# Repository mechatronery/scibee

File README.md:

<table>
  <tr>
    <td width="120" align="center">
      
    </td>
    <td>
      <h1>Smart Community Integrated Beehive (SCIBee)</h1>
    </td>
  </tr>
</table>

SCIBee is an integrated beekeeping monitoring and management system combining beehive sensors, automated control hardware, entrance monitoring, camera-based bee detection, data aggregation, and AI-assisted colony assessment. It integrates local observations with agricultural and community data to support colony monitoring, seasonal assessment, and identification of potential risks, including Varroa mite infestations.

The system combines embedded controllers, Raspberry Pi computers, Python services, locally hosted AI models, and [OpenAgri](https://horizon-openagri.eu/) services. It supports two deployment modes: **Cloud Mode** and **Edge Mode**.

## System Overview

SCIBee consists of several interconnected subsystems:

- **Base Control System** — Measures beehive weight, treatment-agent mass, environmental conditions, and electrical parameters. It also supports automated treatment control.

- **Entrance Monitoring System** — Measures bee traffic, controls the entrance mechanism, and captures images for AI-assisted bee and Varroa monitoring.

- **Base Controller** — Uses a Raspberry Pi Zero 2 W to communicate with the base control boards over I²C, collect measurements, and provide a web interface for monitoring and control.

- **Observation Aggregator** — Processes sensor measurements and camera data, calculates statistics, performs image-based Varroa detection, and creates structured observations.

- **Beehive Evaluator** — Uses Qwen3-4B with `llama.cpp` to analyze aggregated observations and generate colony assessments and risk summaries.

- **OpenAgri Integration** — Connects SCIBee to Farm Calendar and related agricultural services for observations, weather data, and risk assessments.

- **Community Information System** — Collects community observations about flowering plants, meadow management, Varroa, and pesticide spraying.

- **Synchroniser** — Used for manual transfer of online observations to the Edge system.

- **Presenter** — Displays the latest AI-generated beehive evaluation retrieved from Farm Calendar.

The deployment mode determines where processing and AI inference run and whether external data integrations are directly available to the Aggregator.

## Deployment Modes

SCIBee supports two deployment modes that share the core beehive monitoring hardware and software but differ in processing infrastructure, connectivity, and data integration.

### Edge Mode

Edge Mode runs the main processing services and AI inference locally, close to the beehive powered exclusively by solar power.

- A Raspberry Pi Zero 2 W acts as the local base controller.
- A Raspberry Pi 5 hosts the Data Aggregator, Beehive Evaluator, Qwen3-4B inference server, and supporting services.
- The Raspberry Pi devices communicate over a local network.
- Sensor measurements and camera data are processed locally.
- Weather, risk, and community data integrations that require internet access are not available to the Aggregator.
- Observations from an online server can be transferred to the local Observation Store using a manually transferred synchronization file.

**Architecture:**

```mermaid
flowchart TB
    B["Beehive Sensors and Base Control Boards"]
    C["Entrance Camera — ESP32-S3-EYE"]
    EC["Entrance Counter — ESP32-C3"]

    G["Base Controller — Raspberry Pi Zero 2 W"]

    subgraph EDGE["Edge System — Raspberry Pi 5"]
        A["Data Aggregator<br/>(Local Observations)"]
        S[("Observation Store<br/>(OA-FarmCalendar)")]
        Y["Synchronizer"]
        E["Beehive Evaluator"]
        L["Qwen3-4B Inference Server<br/>llama.cpp"]
        P["Presenter"]
    end

    subgraph ONLINE["Online Server"]
        W["Weather and Risk Data<br/>(OA-WeatherService & PestAndDiseaseManagement)"]
        M["Community Observations"]
        OA["Data Aggregator<br/>(External Data)"]
        OS[("Observation Store<br/>(OA-FarmCalendar)")]

        W -->|"Weather and risk data"| OA
        M -->|"Community observations"| OA
        OA -->|"Aggregate and store observations"| OS
    end

    BK["Beekeeper"]

    B -->|"Sensor measurements"| G
    C -->|"Captured images / bee detections"| G
    EC -->|"Bee counts and entrance data"| G

    G -->|"Sensor data and images"| A

    A -->|"Store local aggregated observations"| S
    S -->|"Aggregated observations"| E

    OS -->|"Export synchronization file"| BK
    BK -->|"Manual file transfer"| Y
    Y -->|"Import observations"| S

    E <-->|"Inference requests / responses"| L
    E -->|"Generated colony summary"| P
    P -->|"Display summary"| BK

    classDef local fill:#dcefe3,stroke:#328052,color:#163c26
    classDef internet fill:#ffdada,stroke:#d62728,color:#8b1010
    classDef user fill:#fff0d1,stroke:#bd8a28,color:#63430b
    classDef online fill:#e0eaf9,stroke:#4778b8,color:#17365e

    class A,S,Y,E,L,P local
    class W,M internet
    class BK user
    class OA,OS,G online
```

### Cloud Mode

In Cloud Mode beehive data is collected by a remotely hosted processing environment.

- A Raspberry Pi Zero 2 W acts as the local base controller.
- A SIM7600G-H cellular modem provides LTE connectivity.
- A single cloud virtual machine hosts the Data Aggregator, Observation Store, Beehive Evaluator, and Qwen3-4B inference server.
- The Aggregator can integrate beehive data, external weather forecasts, risk assessments, and community observations.
- Tailscale provides private network connectivity for remote administration and access to connected devices and services.

**Architecture:**

```mermaid
flowchart TB
    B["Beehive Sensors and Base Control Boards"]
    C["Entrance Camera — ESP32-S3-EYE"]
    EC["Entrance Counter — ESP32-C3"]
    G["Base Controller — Raspberry Pi Zero 2 W"]
    N["LTE / Internet Connectivity"]

    subgraph CLOUD["Cloud System — Single Virtual Machine"]
        W["Weather and Risk Data<br/>(OA-WeatherService & PestAndDiseaseManagement)"]
        M["Community Observations"]
        A["Data Aggregator"]
        S[("Observation Store<br/>(OA-FarmCalendar)")]
        E["Beehive Evaluator"]
        L["Qwen3-4B Inference Server<br/>llama.cpp"]
        P["Presenter"]

        W -->|"Weather and risk data"| A
        M -->|"Community observations"| A
        A -->|"Aggregate and store observations"| S
        S -->|"Aggregated observations"| E
        E <-->|"Inference requests / responses"| L
        S -->|"Generated colony summary"| P
    end

    BK["Beekeeper"]

    B -->|"Sensor measurements"| G
    C -->|"Captured images / bee detections"| G
    EC -->|"Bee counts and entrance data"| G

    G -->|"Data transfer"| N
    N -->|"Sensor data and images"| A

    P -->|"Display summary"| BK

    classDef local fill:#dcefe3,stroke:#328052,color:#163c26
    classDef internet fill:#ffdada,stroke:#d62728,color:#8b1010
    classDef user fill:#fff0d1,stroke:#bd8a28,color:#63430b
    classDef network fill:#e0eaf9,stroke:#4778b8,color:#17365e

    class A,S,E,L,P local
    class W,M internet
    class BK user
    class G,N network
```

### Cloud vs. Edge

| Aspect                      | Cloud Mode              | Edge Mode                                                   |
| --------------------------- | ----------------------- | ----------------------------------------------------------- |
| Base controller             | Raspberry Pi Zero 2 W   | Raspberry Pi Zero 2 W                                       |
| Processing infrastructure   | Remote virtual machine  | Local Raspberry Pi 5                                        |
| Controller connectivity     | LTE modem               | Local Wi-Fi network                                         |
| AI inference                | Cloud server            | Local Raspberry Pi 5                                        |
| Weather and risk evaluation | Supported               | Skipped when observations are missing                       |
| Synchronization             | Automatic data transfer | Manual synchronization file transfer from the online server |
| Internet requirement        | Required                | Not required (only for online data)                         |

**Key distinction:** Cloud Mode centralizes processing and supports online data integrations. Edge Mode runs processing and AI inference locally, reducing dependence on remote infrastructure for core monitoring and evaluation, but requires manual synchronization of online observations.

## Hardware and Embedded Systems

### Base Control System

The Base Control System monitors beehive weight, treatment-agent mass, environmental conditions, and electrical parameters. Dedicated control boards communicate with the Raspberry Pi Zero 2 W over I²C.

- [Base Control System — Architecture and Hardware](SCIBee_Base/scibee_base_control_system.md)
- [Base Control Board — Firmware and I²C Protocol](SCIBee_Base/scibee_base_control_board_firmware.md)
- [Base Controller — Python Backend and Web Interface](SCIBee_Base/scibee_base_controller.md)
- [Base Stand — Mechanical Design](SCIBee_Base/scibee_base_stand.md)

### Entrance Monitoring System

The Entrance Monitoring System combines bee-traffic measurement, entrance control, and camera-based image capture.

The ESP32-C3-based entrance counter collects measurements from the entrance corridor array and controls the entrance mechanism. A separate ESP32-S3-EYE camera module captures images for AI-assisted bee detection and subsequent analysis.

- [Entrance System — Architecture and Hardware](SCIBee_Entrance/scibee_entrance_system.md)
- [Entrance Counter Corridor — Mechanical and Electrical Design](SCIBee_Entrance/scibee_entrance_counter_corridor.md)
- [Entrance Counter Corridor — Firmware](SCIBee_Entrance/scibee_entrance_counter_corridor_firmware.md)
- [Entrance Counter — Firmware](SCIBee_Entrance/scibee_entrance_counter_firmware.md)
- [Entrance Camera — Firmware and AI Detection](SCIBee_Entrance/scibee_entrance_camera_firmware.md)
- [Entrance and Camera — Firmware Programming Guide](SCIBee_Entrance/scibee_entrance_firmware_programming.md)

## Software Services and Data Processing

### Data Aggregator

The Data Aggregator collects beehive sensor measurements and camera data, calculates statistics, performs image-based Varroa detection, and creates structured observations in Farm Calendar.

Its execution mode determines whether external weather forecasts, risk assessments, and community observations are included.

See [SCIBee Aggregator](SCIBee_Data_Aggregator/scibee_aggregator.md).

### Beehive Evaluator

The Beehive Evaluator retrieves aggregated observations and submits them to a locally hosted Qwen3-4B language model through `llama.cpp`. It generates a structured assessment of colony conditions, seasonal development, and potential risks, then stores the result in Farm Calendar or the configured observation store.

See [SCIBee Evaluator](SCIBee_Evaluator/scibee_evaluator.md).

### OpenAgri Integration

The OpenAgri helper modules provide reusable Python functionality for interacting with agricultural services through REST APIs.

See [SCIBee Helper Functions for OpenAgri Services](SCIBee_OA_Functions/oa_functions.md).

### Community Information System

The Community Information System collects and shares local environmental information relevant to beekeeping, including flowering observations, meadow management, Varroa reports, and pesticide spraying.

See [SCIBee Community](SCIBee_Community/scibee_community.md).

### Synchroniser

The Synchroniser enables manual transfer of online observations to the local Edge Observation Store using a JSON file.

See [SCIBee Synchroniser](SCIBee_Synchroniser/scibee_synchroniser.md).

### Presenter

The Presenter retrieves the latest AI-generated beehive evaluation from Farm Calendar and displays the assessment details and evaluation age for a selected beehive.

See [SCIBee Presenter](SCIBee_Presenter/scibee_presenter.md).

## Getting Started

1. **Choose a deployment mode.** Use Cloud Mode for remote processing and online data integrations, or Edge Mode for local processing and AI inference.
2. **Configure the hardware.** Follow the relevant setup guide for the Raspberry Pi devices, networking, and required services.
3. **Deploy the Base Controller.** Configure I²C communication with the base control boards and verify local monitoring and control.
4. **Configure the software services.** Deploy the Aggregator and Evaluator, configure their service endpoints and execution mode, and set up the required OpenAgri services.
5. **Verify the data flow.** Confirm that sensor measurements and camera data are collected, observations are aggregated, and AI-generated evaluations are stored and available to the presentation layer.

**Note:** The system is **not yet plug-and-play**. Configuration must be reviewed and adapted to the specific hardware arrangement and network setup. Configuration examples may contain placeholder credentials, IP addresses, hostnames, and service URLs. Replace these with values appropriate for your deployment.

## Documentation Index

| Document                                                                                           | Description                                                                        |
| -------------------------------------------------------------------------------------------------- | ---------------------------------------------------------------------------------- |
| [Cloud Raspberry Pi Gateway Setup](SCIBee_Setup_Cloud/scibee_setup_cloud_rpi.md)                   | Gateway configuration, LTE connectivity, Tailscale, and Base Controller deployment |
| [Cloud Server Setup](SCIBee_Setup_Cloud/scibee_setup_cloud_server.md)                              | Virtual machine, Docker, AI inference, and service deployment                      |
| [Edge Raspberry Pi Setup](SCIBee_Setup_Edge/scibee_setup_edge_rpi.md)                              | Local networking, Raspberry Pi 5, AI inference, and service deployment             |
| [Observation Aggregator](SCIBee_Data_Aggregator/scibee_aggregator.md)                              | Data collection, processing modes, and observation integration                     |
| [Beehive Evaluator](SCIBee_Evaluator/scibee_evaluator.md)                                          | AI-based evaluation of aggregated beehive observations                             |
| [Base Controller](SCIBee_Base/scibee_base_controller.md)                                           | Python backend, web interface, measurement logging, and control                    |
| [Base Control System](SCIBee_Base/scibee_base_control_system.md)                                   | Hardware architecture and measurement components                                   |
| [Base Control Board Firmware](SCIBee_Base/scibee_base_control_board_firmware.md)                   | Embedded firmware and I²C command protocol                                         |
| [Base Stand](SCIBee_Base/scibee_base_stand.md)                                                     | Mechanical design and structural components                                        |
| [Entrance System](SCIBee_Entrance/scibee_entrance_system.md)                                       | Entrance monitoring hardware and architecture                                      |
| [Entrance Counter Corridor](SCIBee_Entrance/scibee_entrance_counter_corridor.md)                   | Corridor structure, electronics, and sensor arrangement                            |
| [Entrance Counter Corridor Firmware](SCIBee_Entrance/scibee_entrance_counter_corridor_firmware.md) | Corridor sensor firmware and I²C protocol                                          |
| [Entrance Counter Firmware](SCIBee_Entrance/scibee_entrance_counter_firmware.md)                   | Bee counting, entrance control, and data logging                                   |
| [Entrance Camera Firmware](SCIBee_Entrance/scibee_entrance_camera_firmware.md)                     | Camera operation, AI detection, image capture, and storage                         |
| [Firmware Programming Guide](SCIBee_Entrance/scibee_entrance_firmware_programming.md)              | Development environment, firmware uploads, and board configuration                 |
| [OpenAgri Helper Functions](SCIBee_OA_Functions/oa_functions.md)                                   | Python utilities for OpenAgri REST APIs                                            |
| [Community Information System](SCIBee_Community/scibee_community.md)                               | Community applications, architecture, and data handling                            |
| [Synchroniser](SCIBee_Synchroniser/scibee_synchroniser.md)                                         | Manual transfer of online observations to the Edge system                          |
| [Presenter](SCIBee_Presenter/scibee_presenter.md)                                                  | Displays the latest AI-generated beehive evaluation                                |

## Notes

- **Network configuration:** Use IP addresses, subnets, hostnames, and service URLs appropriate to your deployment.
- **Time synchronization:** Services and embedded devices use UTC timestamps. Ensure that clocks are synchronized and time settings are configured consistently across devices and services.
- **Treatment decisions:** Sensor measurements and AI-generated assessments are decision-support tools. Follow applicable product instructions and veterinary guidance when making treatment decisions.

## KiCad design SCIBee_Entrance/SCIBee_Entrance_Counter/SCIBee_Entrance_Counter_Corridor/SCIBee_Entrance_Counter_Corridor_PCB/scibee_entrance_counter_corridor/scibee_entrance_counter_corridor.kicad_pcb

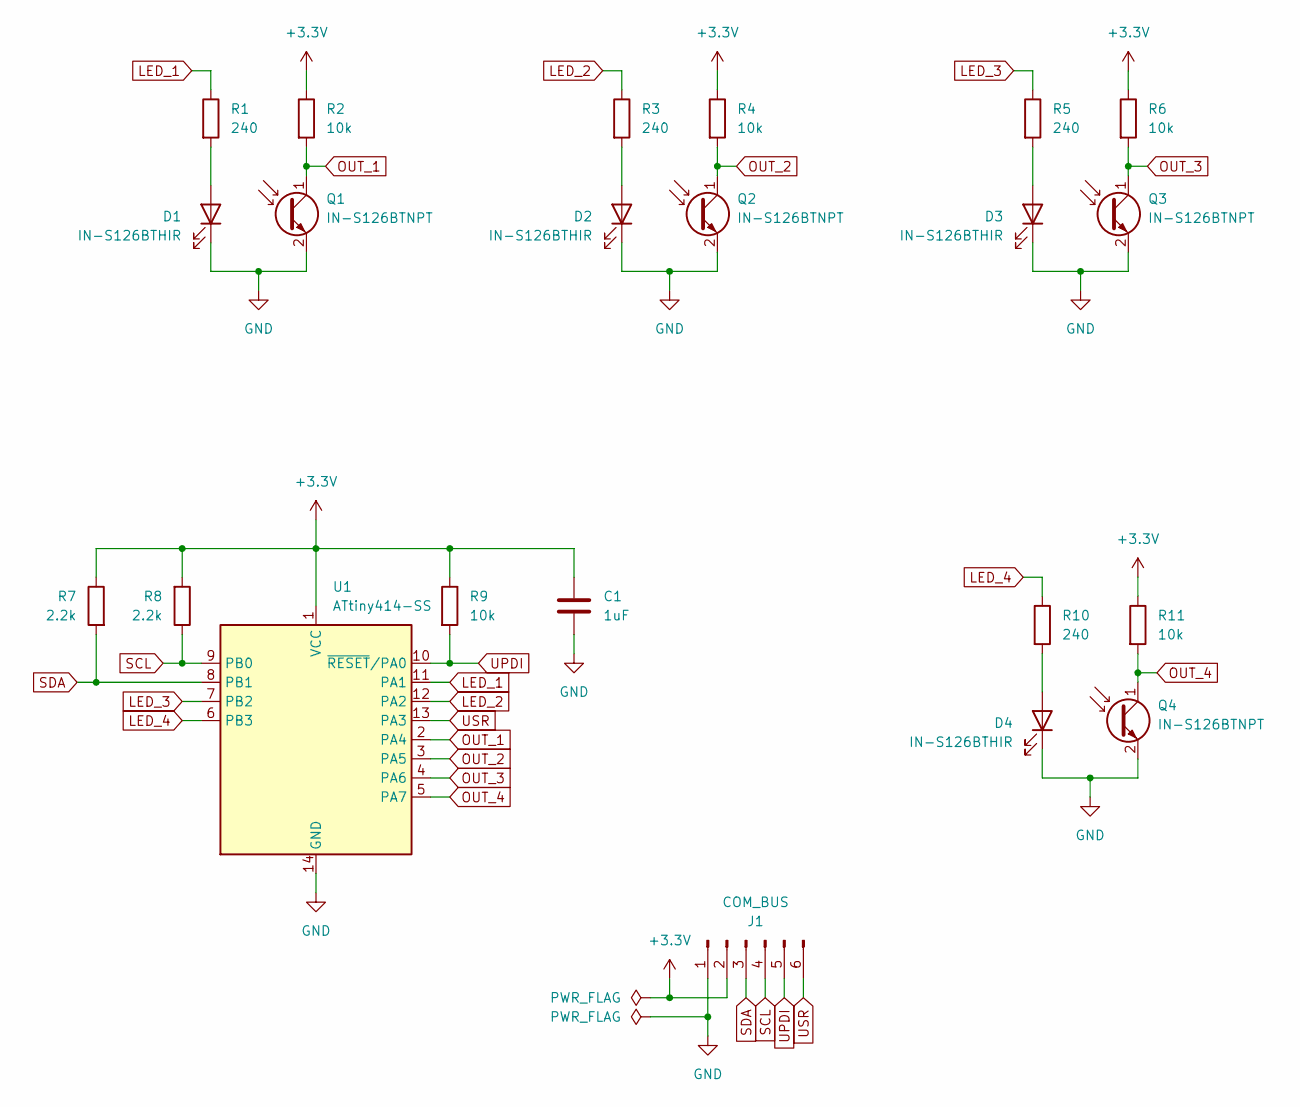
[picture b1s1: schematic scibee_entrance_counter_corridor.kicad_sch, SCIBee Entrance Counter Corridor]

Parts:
C1: 1uF; C_1206_3216Metric_Pad1.33x1.80mm_HandSolder
D1, D2, D3, D4: IN-S126BTHIR; LED_1206_3216Metric_Pad1.42x1.75mm_HandSolder
J1: COM_BUS; PinSocket_1x06_P2.54mm_Vertical
Q1, Q2, Q3, Q4: IN-S126BTNPT; LED_1206_3216Metric_Pad1.42x1.75mm_HandSolder
R1, R3, R5, R10: 240; R_1206_3216Metric_Pad1.30x1.75mm_HandSolder
R2, R4, R6, R9, R11: 10k; R_1206_3216Metric_Pad1.30x1.75mm_HandSolder
R7, R8: 2.2k; R_1206_3216Metric_Pad1.30x1.75mm_HandSolder
U1: ATtiny414-SS; SOIC-14_3.9x8.7mm_P1.27mm

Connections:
+3.3V: C1.2, J1.2, R2.1, R4.1, R6.1, R7.1, R8.2, R9.1, R11.1, U1.1 (VCC)
GND: C1.1, D1.1 (K), D2.1 (K), D3.1 (K), D4.1 (K), J1.1, Q1.2 (E), Q2.2 (E), Q3.2 (E), Q4.2 (E), U1.14 (GND)
LED_1: R1.1, U1.11 (PA1)
LED_2: R3.1, U1.12 (PA2)
LED_3: R5.1, U1.7 (PB2)
LED_4: R10.1, U1.6 (PB3)
unnamed: D1.2 (A), R1.2
unnamed: D2.2 (A), R3.2
unnamed: D3.2 (A), R5.2
unnamed: D4.2 (A), R10.2
OUT_1: Q1.1 (C), R2.2, U1.2 (PA4)
OUT_2: Q2.1 (C), R4.2, U1.3 (PA5)
OUT_3: Q3.1 (C), R6.2, U1.4 (PA6)
OUT_4: Q4.1 (C), R11.2, U1.5 (PA7)
SCL: J1.4, R8.1, U1.9 (PB0)
SDA: J1.3, R7.2, U1.8 (PB1)
UPDI: J1.5, R9.2, U1.10 (~RESET/PA0)
USR: J1.6, U1.13 (PA3)

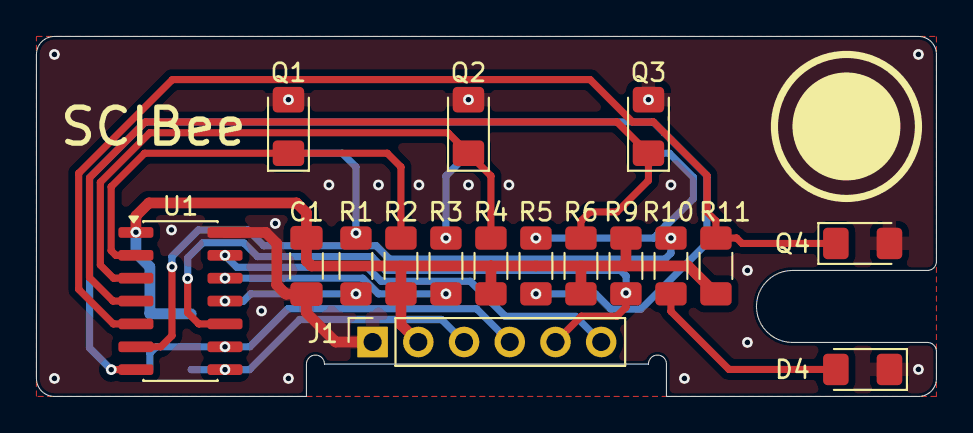
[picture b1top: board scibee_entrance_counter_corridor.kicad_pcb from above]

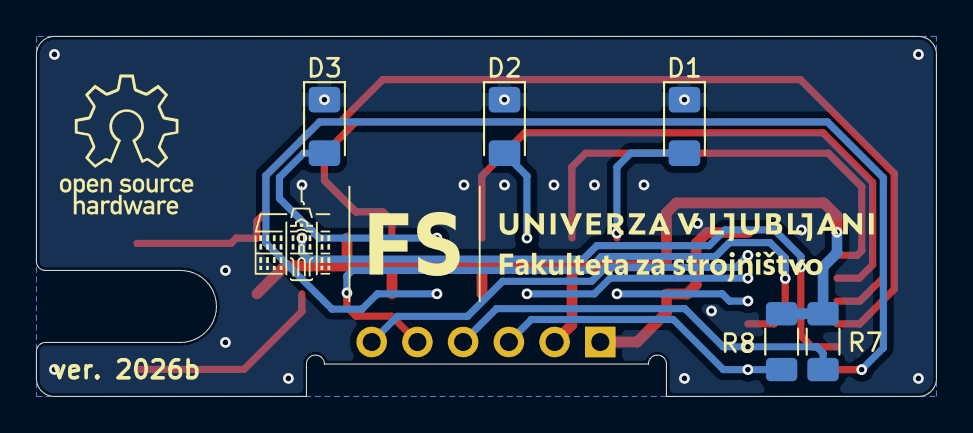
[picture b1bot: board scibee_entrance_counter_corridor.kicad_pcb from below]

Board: 2 copper layers, 50.0 x 20.0 mm, 22 parts (5 on the bottom side), 18 nets.

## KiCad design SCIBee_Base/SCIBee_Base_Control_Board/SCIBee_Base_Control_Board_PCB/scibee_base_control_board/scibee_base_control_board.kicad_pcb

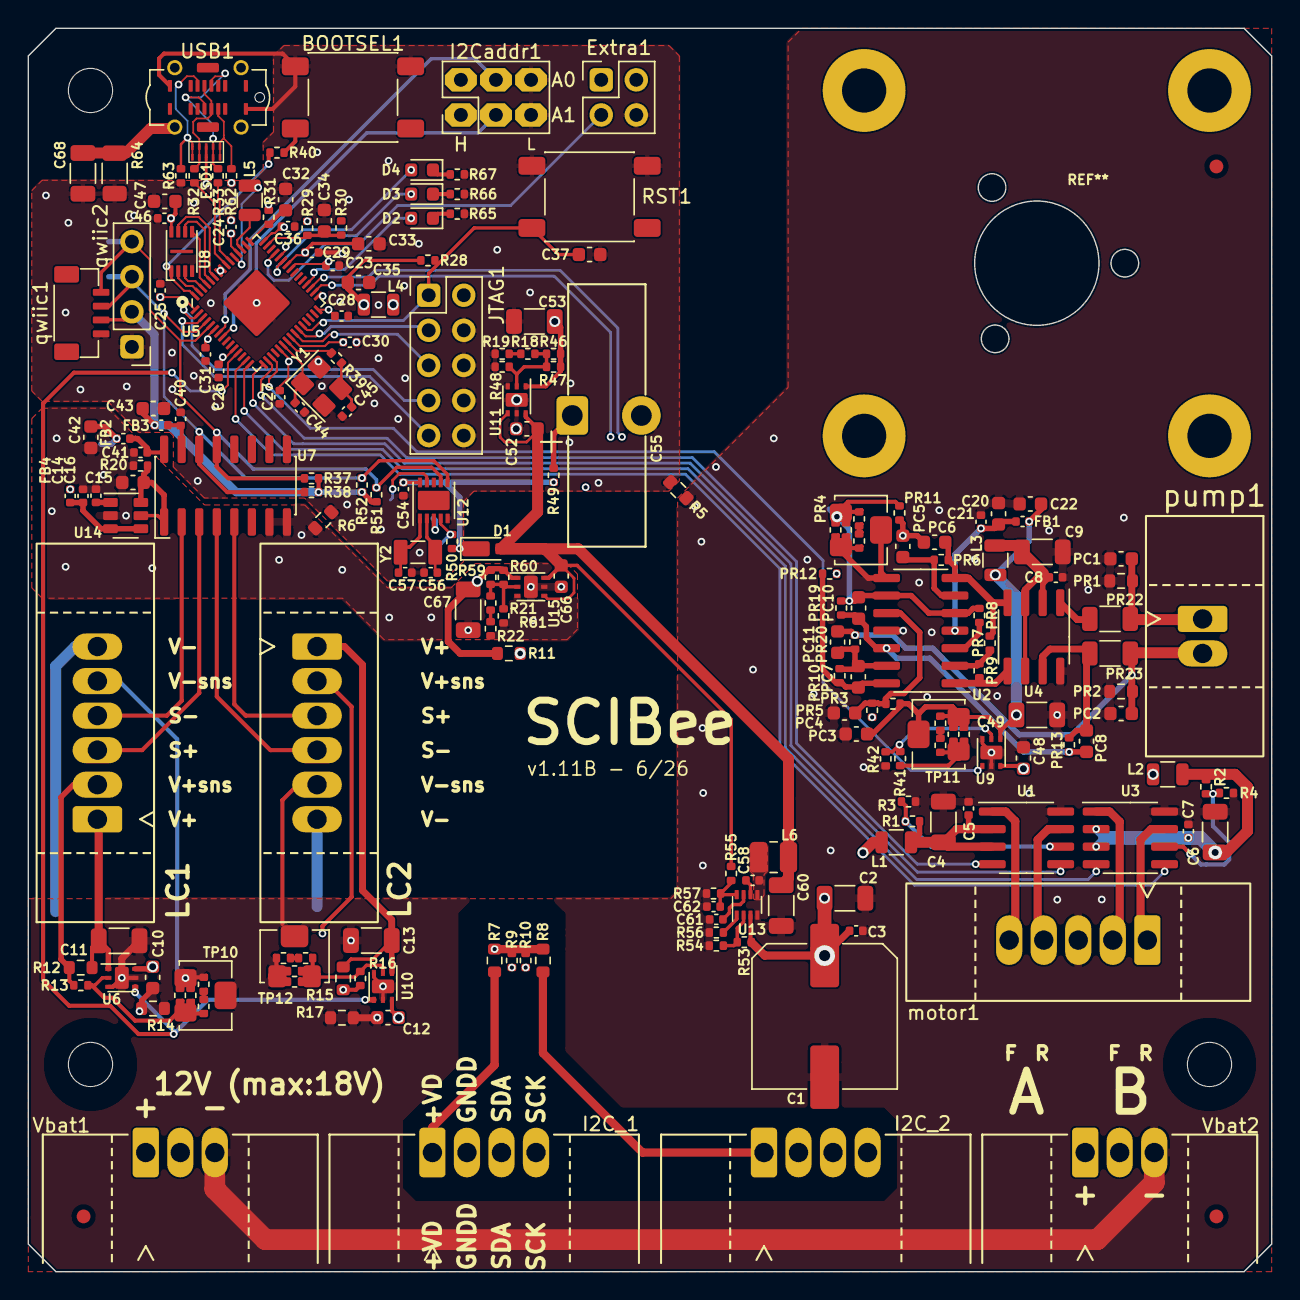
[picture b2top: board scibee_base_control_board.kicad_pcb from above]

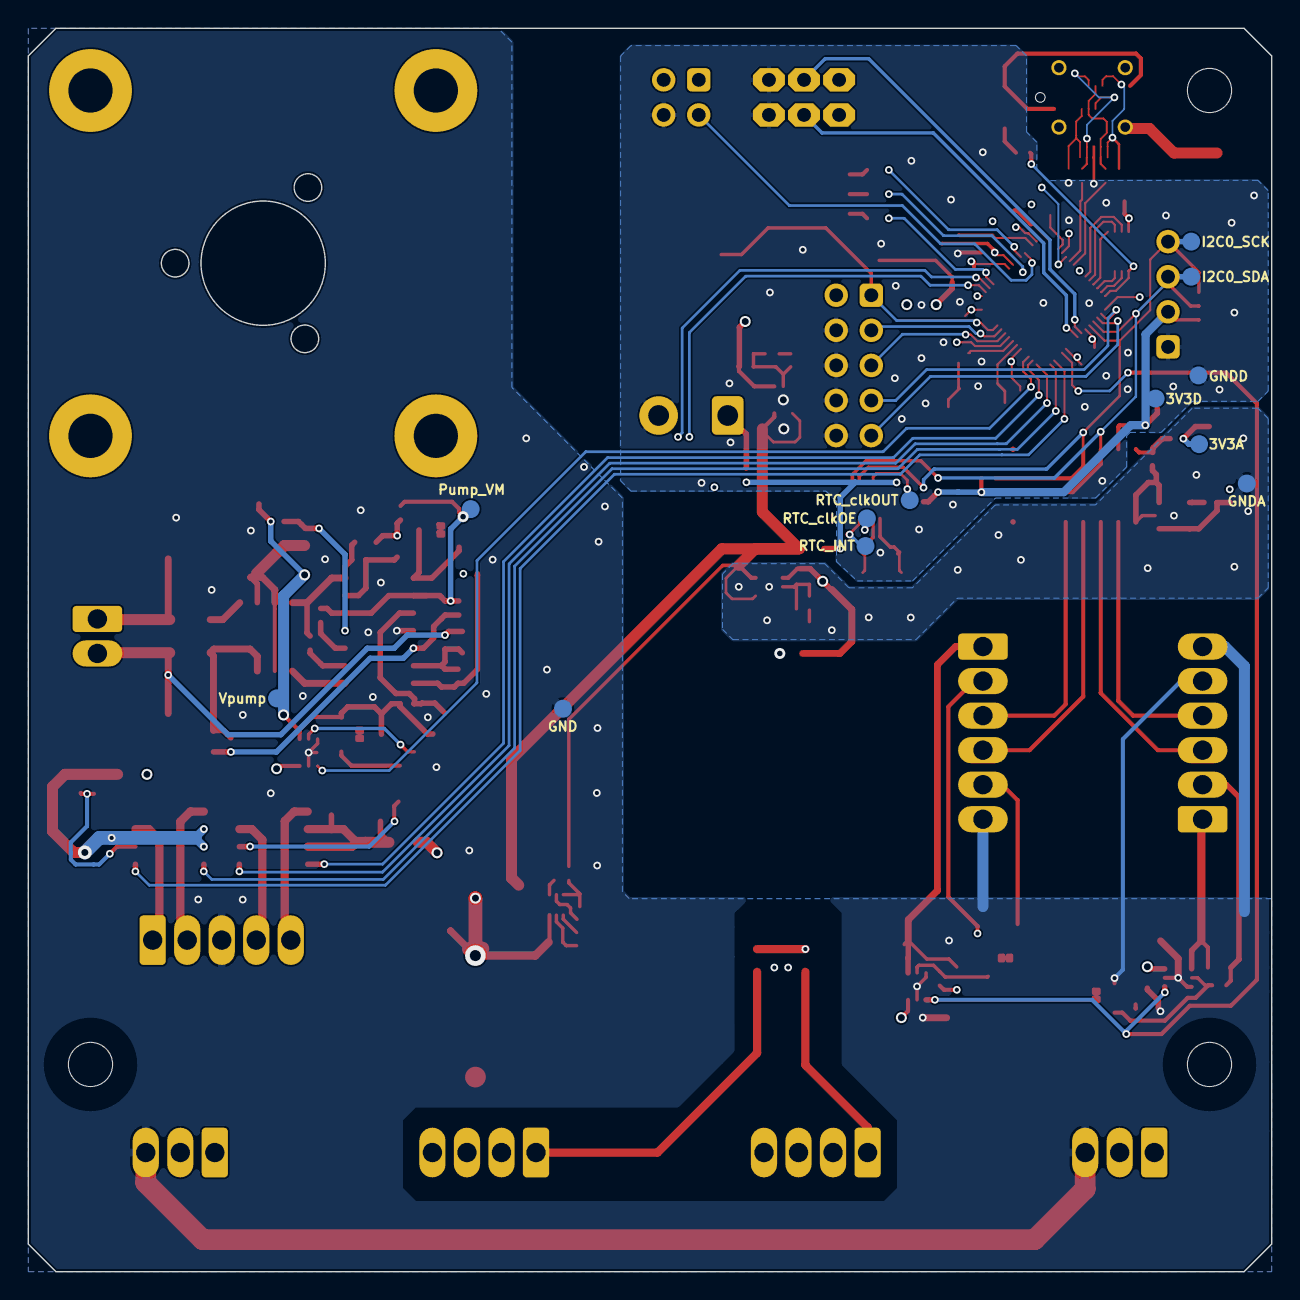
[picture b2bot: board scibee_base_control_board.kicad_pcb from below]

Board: 4 copper layers, 90.0 x 90.0 mm, 208 parts (12 on the bottom side), 118 nets.

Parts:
BOOTSEL1: SW_Momentary_NO; SW_PUSH_6mm_SMD
C1: Capacitor_pol; C_AlElec_SMD-10x10.2
C2, C4, C6, C9, C11, C13, C49, C53, C60, C67: 10uF; C_1206_(3216)
C3, C5, C7, C8, C14, C16, C21, C23, C24, C25, C26, C27, C28, C29, C30, C31, C36, C40, C41, C46, C54, C58, C61: 100nF; C_0402_(1005)
C10, C12, C15, C20, C22, C37, C42, C43, C48, C52, C66: 1uF; C_0603_(1608)
C32, C33, C34, C35, C47: 4u7F; C_0603_(1608)
C44, C45: 15pF; C_0402_(1005)
C55: 1F; C_Supercap_D18.7mm_P5.00mm_Vertical
C56, C57: -; C_0402_(1005)
C62: cap; C_0402_(1005)
C68: 2n2F; C_1206_(3216)
D1: RF05VAM1STR; D_DO-219AD_(microSMP)
D2: red; LED_0603_(1608)
D3: yellow; LED_0603_(1608)
D4: green; LED_0603_(1608)
ESD1: PUSB3FA2Z; DFN2510A-10
Extra1: 0.1" 2x2 header; Header_Pin_THT_Vertical_P2.54mm_2x02
FB1, FB2, FB3, FB4: FB600; L_0402_(1005)
FID1, FID2, FID3: Fiducial; Fiducial_1mm+2mm
I2C_1, I2C_2: TerminalBlock_2.5mm_Horizontal; TerminalBlock_1x04_P2.5mm_Horizontal_Screw
I2Caddr1: 0.1" 2x03 header; Header_Pin_THT_Vertical_P2.54mm_2x03
JTAG1: Conn_02x05; Header_Pin_THT_Vertical_P2.54mm_2x05
L1, L2, L3, L4, L5: 4u7H; L_0806_(2016)
L6: 22uH; L_1008_(2520)
LC1, LC2: TerminalBlock_2.5mm_Horizontal; TerminalBlock_1x06_P2.5mm_Vertical_Screw
M1, M3, M4: Mounting_hole; MountingHole_M3
PC1, PC2: 15pF; C_0603_(1608)
PC3, PC4: 1uF; C_0603_(1608)
PC5, PC6: 1nF; C_0603_(1608)
PC7, PC10: 10pF; C_0603_(1608)
PC8, PC11: 100pF; C_0603_(1608)
PR1, PR2: 1M; R_0603_(1608)
PR3, PR5, PR10, PR19: 470k; R_0402_(1005)
PR4: 10k; PVG5A
PR6: 68k; R_0402_(1005)
PR7, PR8, PR9: 10k; R_0402_(1005)
PR11: 390; R_0402_(1005)
PR12, PR13, PR20: 1k5; R_0402_(1005)
PR22, PR23: 10; R_1206_(3216)
R1, R2: 0; R_0402_(1005)
R3, R4, R30: -; R_0402_(1005)
R5, R6, R11: 0; R_0603_(1608)
R7, R8, R12, R14, R15, R17: -; R_0603_(1608)
R9, R10, R18, R21, R37, R38, R51, R52, R62, R63: 5k1; R_0402_(1005)
R13, R16, R41, R46, R47, R59, R60: 470k; R_0402_(1005)
R19, R22, R28, R42, R48, R61: 68k; R_0402_(1005)
R20, R50, R54, R56, R57: 10k; R_0402_(1005)
R29: 390R; R_0402_(1005)
R31, R32, R33: 27R; R_0402_(1005)
R39, R40: 1k5; R_0402_(1005)
R49, R65, R66, R67: 390; R_0402_(1005)
R53, R55: 39k; R_0402_(1005)
R64: 1M; R_1206_(3216)
RST1: SW_Momentary_NO; SW_PUSH_6mm_SMD
TP1: 3V3D; TestPoint
TP2: Pump_VM; TestPoint
TP3: 3V3A; TestPoint
TP4: GND; TestPoint
TP5: I2C0_SDA; TestPoint
TP6: I2C0_SCK; TestPoint
TP7: RTC_INT; TestPoint
TP8: RTC_clkOE; TestPoint
TP9: RTC_clkOUT; TestPoint
TP10, TP11, TP12: 500k; PVG5A
TP13: GNDA; TestPoint
TP14: GNDD; TestPoint
TP15: Vpump; TestPoint
U1, U3, U4: BD6231F-E2; SOIC-8_3.9x4.9mm_P1.27mm
U2: NCV274; SOIC-14_3.9x8.7mm_P1.27mm
U5: RP2350A; QFN-60-EP1_7x7mm_P0.4mm_EP3.4mm
U6, U9, U10, U11, U15: TPS7A2601; DFN-6-1EP_2x2mm_P0.65mm
U7: NAU7802SGI; SOIC-16_3.9x9.9mm_P1.27mm
U8: W25Q32RV; XSON-8-EP_2x3mm_P0.5mm_EP0.2x1.6mm
U12: PCF85063A; DFN-10_2.6x2.6_P0.5
U13: TPS62932; SOT-5X3-8
U14: MAX6070BAUT21+T; SOT-23-6
USB1: USB_C_USB2.0; USB_C_GCT_USB4220_Vertical
Vbat1, Vbat2: TerminalBlock_2.5mm_Horizontal; TerminalBlock_1x03_P2.5mm_Horizontal_Screw
Y1: 12MHz; Crystal_SMD_3225-4Pin_3.2x2.5mm
Y2: 32.768kHz; Crystal_SMD_TXC_9HT10
motor1: TerminalBlock_2.5mm_Horizontal; TerminalBlock_1x05_P2.5mm_Vertical_Screw
pump1: TerminalBlock_2.5mm_Vertical; TerminalBlock_1x02_P2.5mm_Vertical_Screw
qwiic1: SIO_SPARKFUN_qwiic; JST_SMD_Vertical_P1.00mm_BM04B
qwiic2: Conn_01x04; Header_Pin_THT_Vertical_P2.54mm_1x04

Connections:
+3.3VA: C42.1, C67.1, FB2.1, FB4.1, R11.2, R59.1, R60.1, TP3.1, U15.1 (Vout)
+3.3VD: C43.1, C53.1, Extra1.1, FB3.1, I2Caddr1.1, I2Caddr1.2, JTAG1.2, L4.2, R7.1, R8.1, R9.1, R10.1, R11.1, R37.1, R38.1, R46.1, R47.1, R51.1, R52.1, TP1.1, U11.1 (Vout), qwiic1.2 (3V3), qwiic2.2
+Vbat: C1.+, C2.1, C3.1, C10.1, C12.1, C48.1, L1.1, L2.1, R53.2, U6.6 (Vin), U9.6 (Vin), U10.6 (Vin), U13.3 (Vin), Vbat1.1, Vbat2.1
/+4V: C52.1, C60.1, C66.1, D1.A, L6.2, R55.1, U11.4 (EN), U11.6 (Vin), U15.4 (EN), U15.6 (Vin)
/H-bridge/VrefA: R1.2, R3.1, U1.6 (Vref)
/H-bridge/VrefB: R2.2, R4.1, U3.6 (Vref)
/I2C0_SCK: R37.2, R51.2, TP6.1, U5.5 (GPIO_3/SPI0_MOSI/UART0_RTS/I2C1_SCL/PWM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), U7.13 (SCK), U12.7 (SCL), qwiic1.4 (SCK), qwiic2.4
/I2C0_SDA: R38.2, R52.2, TP5.1, U5.4 (GPIO_2/SPI0_SCK/UART0_CTS/I2C1_SDA/PWM1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), U7.14 (SDA), U12.6 (SDA), qwiic1.3 (SDA), qwiic2.3
/I2C1_SCK: I2C_1.4, I2C_2.4, R10.2, U5.33 (GPIO_21/SPI0_CSn/UART1_RX/I2C0_SCL/PWM2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)
/I2C1_SDA: I2C_1.3, I2C_2.3, R9.2, U5.32 (GPIO_20/SPI0_MISO/UART1_TX/I2C0_SDA/PWM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)
/LC_enable: U5.12 (GPIO_8/SPI1_MISO/UART1_TX/I2C0_SDA/PWM4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), U6.4 (EN), U10.4 (EN)
/Load cell ADC I2C/Load cell Supply 1/+Vout: C11.1, LC1.1, R12.1, U6.1 (Vout)
/Load cell ADC I2C/Load cell Supply 1/+Vsns: LC1.2, R12.2, R13.1
/Load cell ADC I2C/Load cell Supply 2/+Vout: C13.1, LC2.1, R15.1, U10.1 (Vout)
/Load cell ADC I2C/Load cell Supply 2/+Vsns: LC2.2, R15.2, R16.1
/Load cell ADC I2C/Voltage reference/Aref: C15.1, R20.1, U7.1 (refP), U14.5 (OUTs), U14.6 (OUT)
/MOT_AF: U1.4 (Fin), U5.17 (GPIO_13/SPI1_CSn/UART0_RX/I2C0_SCL/PWM6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)
/MOT_AR: U1.5 (Rin), U5.16 (GPIO_12/SPI1_MISO/UART0_TX/I2C0_SDA/PWM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)
/MOT_BF: U3.4 (Fin), U5.15 (GPIO_11/SPI1_MOSI/UART1_RTS/I2C1_SCL/PW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)
/MOT_BR: U3.5 (Rin), U5.14 (GPIO_10/SPI1_SCK/UART1_CTS/I2C1_SDA/PWM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)
/PMP_enable: U5.18 (GPIO_14/SPI1_SCK/UART0_CTS/I2C1_SDA/PWM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), U9.4 (EN)
/Procesor/1V1: C29.1, C30.1, C31.1, C33.1, L5.2, U5.6 (DVDD), U5.23 (DVDD), U5.39 (DVDD), U5.50 (VREG_FB)
/Procesor/GPIO0: JTAG1.7, U5.2 (GPIO_0/SPI0_MISO/UART0_TX/I2C0_SDA/PWM0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)
/Procesor/GPIO1: JTAG1.9, U5.3 (GPIO_1/SPI0_CSn/UART0_RX/I2C0_SCL/PWM0_B)
/Procesor/GPIO4: I2Caddr1.4, U5.7 (GPIO_4/SPI0_MISO/UART1_TX/I2C0_SDA/PWM2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)
/Procesor/GPIO5: I2Caddr1.3, U5.8 (GPIO_5/SPI0_CSn/UART1_RX/I2C0_SCL/PWM2_B)
/Procesor/GPIO19: Extra1.2, U5.31 (GPIO_19/SPI0_MOSI/UART0_RTS/I2C1_SCL/PW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)
/Procesor/GPIO22: D2.A, U5.34 (GPIO_22/SPI0_SCK/UART1_CTS/I2C1_SDA/PWM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)
/Procesor/GPIO26/ADC0: D3.A, U5.40 (GPIO_26/ADC0/SPI1_SCK/UART1_CTS/I2C1_SD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)
/Procesor/GPIO27/ADC1: D4.A, U5.41 (GPIO_27/ADC1/SPI1_MOSI/UART1_RTS/I2C1_S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)
/Procesor/GPIO28/ADC2: Extra1.3, U5.42 (GPIO_28/ADC2/SPI1_RX/UART0_TX/I2C0_SDA/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)
/Procesor/QSPI_SCLK: U5.56 (QSPI_SCLK), U8.6 (CLK)
/Procesor/QSPI_SD0: U5.57 (QSPI_SD0), U8.5 (MOSI/IO0)
/Procesor/QSPI_SD1: U5.59 (QSPI_SD1), U8.2 (MISO/IO1)
/Procesor/QSPI_SD2: U5.58 (QSPI_SD2), U8.3 (~WP/IO2)
/Procesor/QSPI_SD3: U5.55 (QSPI_SD3), U8.7 (~HOLD/~RST/IO3)
/Procesor/QSPI_SS: R40.1, U5.60 (QSPI_CSn), U8.1 (~CS)
/Procesor/RP_CLK/Xin: C44.1, U5.21 (XIN), Y1.1
/Procesor/RP_CLK/Xout: R39.2, U5.22 (XOUT)
/Procesor/RP_FLASH/3V3: C23.1, C24.1, C25.1, C26.1, C27.1, C28.1, C35.1, C36.1, C46.1, C47.1, L4.1, R28.1, R29.2, R31.1, U5.1 (IOVDD), U5.11 (IOVDD), U5.20 (IOVDD), U5.30 (IOVDD), U5.38 (IOVDD), U5.45 (IOVDD), U5.49 (VREG_Vin), U5.53 (USB_VDD), U5.54 (QSPI_IOVDD), U8.8 (VCC)
/Procesor/RUN: C37.1, JTAG1.1, R28.2, RST1.COM, U5.26 (RUN)
/Procesor/SC: JTAG1.5, U5.24 (SWCLK)
/Procesor/SD: JTAG1.3, U5.25 (SWDIO)
/Procesor/USB_N: ESD1.2 (K2), ESD1.9 (K2), R33.1, USB1.A7 (D-), USB1.B7 (D-)
/Procesor/USB_P: ESD1.4 (K3), ESD1.7 (K3), R32.1, USB1.A6 (D+), USB1.B6 (D+)
/Pump driver/Piezo pump regulated suply/+Vout: C22.1, C49.1, FB1.1, L3.1, PC3.1, PR3.1, TP11.C, TP11.S, TP15.1, U9.1 (Vout)
/Pump driver/Vm: PC10.1, PR4.CC, PR8.2, PR11.2, PR19.1, TP2.1, U2.5 (+), U2.9 (-)
/RTC/clkOE: TP8.1, U12.3 (clkOE)
/RTC/clkOUT: TP9.1, U12.9 (clkOUT)
/RTC/~INT: R50.2, TP7.1, U12.4 (~INT)
GND: C1.-, C2.2, C3.2, C4.2, C5.2, C6.2, C7.2, C8.2, C9.2, C10.2, C11.2, C12.2, C13.2, C20.2, C21.2, C22.2, C48.2, C49.2, C60.2, C61.2, C62.2, LC1.5, LC1.6, LC2.5, LC2.6, PC1.2, PC2.2, PC3.2, PC4.2, PR1.1, PR2.1, PR5.2, R3.2, R4.2, R5.2, R14.1, R14.2, R17.1, R17.2, R42.2, R54.2, R56.2, R57.2, TP4.1, TP10.CC, TP10.S, TP12.CC, TP12.S, U1.8 (GND), U2.11 (V-), U3.8 (GND), U4.8 (GND), U6.0 (GND), U6.3 (PG), U6.5 (GND), U9.0 (GND), U9.3 (PG), U9.5 (GND), U10.0 (GND), U10.3 (PG), U10.5 (GND), U13.4 (GND), Vbat1.3, Vbat2.3, motor1.3
GNDA: C14.2, C15.2, C16.2, C41.2, C42.2, C66.2, C67.2, R6.1, R20.2, R22.2, R61.2, TP13.1, U7.7 (refN), U7.8 (AVss), U14.2 (GND), U15.0 (GND), U15.3 (PG), U15.5 (GND)
GNDD: BOOTSEL1.NO, C23.2, C24.2, C25.2, C26.2, C27.2, C28.2, C29.2, C30.2, C31.2, C32.2, C33.2, C34.2, C35.2, C36.2, C37.2, C40.2, C43.2, C44.2, C45.2, C46.2, C47.2, C52.2, C53.2, C54.2, C55.-, C56.2, C57.2, C68.2, ESD1.3 (GND), ESD1.8 (GND), Extra1.4, I2C_1.2, I2C_2.2, I2Caddr1.5, I2Caddr1.6, JTAG1.4, JTAG1.6, JTAG1.8, JTAG1.10, R5.1, R6.2, R19.2, R48.2, R62.2, R63.2, R64.2, R65.2, R66.2, R67.2, RST1.NO, TP14.1, U5.0 (GND), U5.47 (VREG_PGND), U7.9 (DVss), U8.4 (GND), U11.0 (GND), U11.3 (PG), U11.5 (GND), U12.5 (Vss), USB1.A1 (GND), USB1.B1 (GND), Y1.2, Y1.4, qwiic1.1 (GND), qwiic2.1
unnamed: BOOTSEL1.COM, R40.2
unnamed: C4.1, C5.1, L1.2, R1.1, U1.2 (Vcc), U1.3 (Vcc)
unnamed: C6.1, C7.1, L2.2, R2.1, U3.2 (Vcc), U3.3 (Vcc)
unnamed: C45.1, R39.1, Y1.3
unnamed: C55.+, R49.1
unnamed: D2.K, R65.1
unnamed: D3.K, R66.1
unnamed: D4.K, R67.1
unnamed: I2C_1.1, R7.2
unnamed: I2C_2.1, R8.2
unnamed: LC1.3, U7.3 (CH1+)
unnamed: LC1.4, U7.2 (CH1-)
unnamed: LC2.3, U7.5 (CH2+)
unnamed: LC2.4, U7.4 (CH2-)
unnamed: PC5.2, PC6.1, PR11.1, PR12.1
unnamed: PC7.2, PR10.1, PR12.2, U2.14
unnamed: PR4.C, PR4.S, U2.8
unnamed: R18.2, R19.1
unnamed: R21.2, R22.1
unnamed: R41.1, TP11.CC
unnamed: U1.1 (OUT1), motor1.5
unnamed: U1.7 (OUT2), motor1.4
unnamed: PR8.1, U2.3 (+)
unnamed: PR7.2, PR9.2, U2.2 (-)
unnamed: PC5.1, PR6.2, U2.6 (-)
unnamed: PC4.1, PR3.2, PR5.1, U2.10 (+)
unnamed: PC8.1, PC10.2, PR13.1, PR19.2, U2.12 (+)
unnamed: PC7.1, PC11.1, PR10.2, PR20.1, U2.13 (-)
unnamed: C20.1, C21.1, FB1.2, U2.4 (V+)
unnamed: U3.1 (OUT1), motor1.2
unnamed: U3.7 (OUT2), motor1.1
unnamed: PC6.2, PR6.1, PR7.1, U2.7, U4.4 (Fin)
unnamed: PR22.2, U4.1 (OUT1)
unnamed: PC8.2, PR13.2, PR23.2, U4.7 (OUT2)
unnamed: PR9.1, U2.1, U4.5 (Rin)
unnamed: C8.1, C9.1, L3.2, U4.2 (Vcc), U4.3 (Vcc), U4.6 (Vref)
unnamed: C34.1, R29.1, R30.2, U5.44 (AVDD)
unnamed: R33.2, U5.51 (USB_DM)
unnamed: R32.2, U5.52 (USB_DP)
unnamed: C32.1, R31.2, U5.46 (VREG_AVdd)
unnamed: L5.1, U5.48 (VREG_LX)
unnamed: R13.2, TP10.C, U6.2 (fb)
unnamed: C41.1, FB2.2, U7.16 (AVdd)
unnamed: C40.1, FB3.2, U7.15 (DVdd)
unnamed: R41.2, R42.1, U9.2 (fb)
unnamed: R16.2, TP12.C, U10.2 (fb)
unnamed: R18.1, R46.2, R47.2, R48.1, U11.2 (fb)
unnamed: C57.1, U12.1 (OSCI), Y2.2
unnamed: C56.1, U12.2 (OSCO), Y2.1
unnamed: C54.1, D1.K, R49.2, R50.1, U12.10 (Vdd)
unnamed: R53.1, R54.1, U13.2 (EN)
unnamed: C62.1, R55.2, R57.1, U13.8 (FB)
unnamed: C61.1, U13.7 (SS)
unnamed: C58.2, L6.1, U13.5 (SW)
unnamed: C58.1, U13.6 (bst)
unnamed: R56.1, U13.1 (rt)
unnamed: C14.1, FB4.2, U14.3 (EN), U14.4 (Vin)
unnamed: C16.1, U14.1 (filter)
unnamed: R21.1, R59.2, R60.2, R61.1, U15.2 (fb)
unnamed: C68.1, R64.1, USB1.MP (CASE)
unnamed: ESD1.1 (K1), ESD1.10 (K1), R62.1, USB1.A5 (CC1)
unnamed: ESD1.5 (K4), ESD1.6 (K4), R63.1, USB1.B5 (CC2)
unnamed: USB1.A4 (VBUS), USB1.B4 (VBUS)
unnamed: PC1.1, PR1.2, PR22.1, pump1.1
unnamed: PC2.1, PC11.2, PR2.2, PR20.2, PR23.1, pump1.2

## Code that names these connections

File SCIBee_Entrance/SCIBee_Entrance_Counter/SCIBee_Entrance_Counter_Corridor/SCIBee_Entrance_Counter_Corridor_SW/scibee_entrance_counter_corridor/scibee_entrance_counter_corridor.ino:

#include <Wire.h>

// --- I2C SLAVE ADDRESS CONFIGURATION ---
// RANGE FOR 31 BOARDS: 40 to 70 
const int I2C_ADDRESS = 68; 

// --- HARDWARE MAPPING (ATtiny404 Physical Pins) ---
const int LED_PINS[] = {PIN_PA1, PIN_PA2, PIN_PB2, PIN_PB3};
const int NUM_LEDS = 4;
const int IR_PINS[] = {PIN_PA4, PIN_PA5, PIN_PA6, PIN_PA7};
const int NUM_IRS = 4;

// --- I2C Command Bases ---
const byte CMD_LED_ON_BASE = 0x10;  
const byte CMD_LED_OFF_BASE = 0x20; 
const byte CMD_IR_READ_BASE = 0x30; 

/*
 * I2C COMMAND TABLE (12 Commands Total)
 * Master sends 1 byte command to the slave.
 * ----------------------------------------------------------------------
 * | Function | Target | Pin | Command (HEX) | Command (DEC) |
 * ----------------------------------------------------------------------
 * | LED ON   | D1     |  PIN_PA1 | 0x10          | 16            |
 * | LED ON   | D2     |  PIN_PA2 | 0x11          | 17            |
 * | LED ON   | D3     |  PIN_PB2  | 0x12          | 18            |
 * | LED ON   | D4     |  PIN_PB3  | 0x13          | 19            |
 * ----------------------------------------------------------------------
 * | LED OFF  | D1     |  PIN_PA1 | 0x20          | 32            |
 * | LED OFF  | D2     |  PIN_PA2 | 0x21          | 33            |
 * | LED OFF  | D3     |  PIN_PB2  | 0x22          | 34            |
 * | LED OFF  | D4     |  PIN_PB3  | 0x23          | 35            |
 * ----------------------------------------------------------------------
 * | IR READ* | Q0     |  PIN_PA4  | 0x30          | 48            |
 * | IR READ* | Q1     |  PIN_PA5  | 0x31          | 49            |
 * | IR READ* | Q2     |  PIN_PA6  | 0x32          | 50            |
 * | IR READ* | Q3     |  PIN_PA7  | 0x33          | 51            |
 * ----------------------------------------------------------------------
 * *Note: IR READ commands only *prepare* the slave. The Master must then
 * immediately request 1 byte (0-255) to get the scaled analog value.
 */

// Volatile state variable to hold the requested sensor index (0-3) for the read event.
volatile int currentReadChannel = -1; 

// ====================================================================
// SETUP
// ====================================================================

void setup() {
  // Initialize LED pins as outputs (default LOW) and IR pins as analog inputs.
  for (int i = 0; i < NUM_LEDS; i++) {
    pinMode(LED_PINS[i], OUTPUT);
    digitalWrite(LED_PINS[i], LOW);
  }
  for (int i = 0; i < NUM_IRS; i++) {
    pinMode(IR_PINS[i], INPUT);
  }

  // Initialize I2C/TWI as a slave and register handlers.
  Wire.begin(I2C_ADDRESS);
  Wire.onReceive(receiveEvent);
  Wire.onRequest(requestEvent);
}

// ====================================================================
// I2C Event Handlers
// ====================================================================

void receiveEvent(int howMany) {
  if (howMany > 0) {
    byte command = Wire.read();
    int index = -1; 

    // LED ON Commands (0x10-0x13)
    if (command >= CMD_LED_ON_BASE && command < (CMD_LED_ON_BASE + NUM_LEDS)) {
      index = command - CMD_LED_ON_BASE;
      if (index >= 0 && index < NUM_LEDS) {
        digitalWrite(LED_PINS[index], HIGH);
      }
    }
    // LED OFF Commands (0x20-0x23)
    else if (command >= CMD_LED_OFF_BASE && command < (CMD_LED_OFF_BASE + NUM_LEDS)) {
      index = command - CMD_LED_OFF_BASE;
      if (index >= 0 && index < NUM_LEDS) {
        digitalWrite(LED_PINS[index], LOW);
      }
    }
    // IR Read Preparation Commands (0x30-0x33)
    else if (command >= CMD_IR_READ_BASE && command < (CMD_IR_READ_BASE + NUM_IRS)) {
      index = command - CMD_IR_READ_BASE;
      if (index >= 0 && index < NUM_IRS) {
        currentReadChannel = index; 
      }
    }
  }

  // Clear buffer if more bytes were sent than expected (safety check).
  while(Wire.available()) { 
    Wire.read();
  }
}

void requestEvent() {
  if (currentReadChannel >= 0 && currentReadChannel < NUM_IRS) {
    // Read 10-bit value (0-1023)
    int analogValue = analogRead(IR_PINS[currentReadChannel]);
    
    // Scale to 8-bit (0-255) by dividing by 4 (shifting right by 2)
    byte responseByte = (byte)(analogValue >> 2); 

    Wire.write(responseByte);
    
    // Reset the channel marker after successful read.
    currentReadChannel = -1; 
  } else {
    // Return 0x00 if no sensor was prepared for reading.
    Wire.write(0x00);
  }
}

void loop() {
}
